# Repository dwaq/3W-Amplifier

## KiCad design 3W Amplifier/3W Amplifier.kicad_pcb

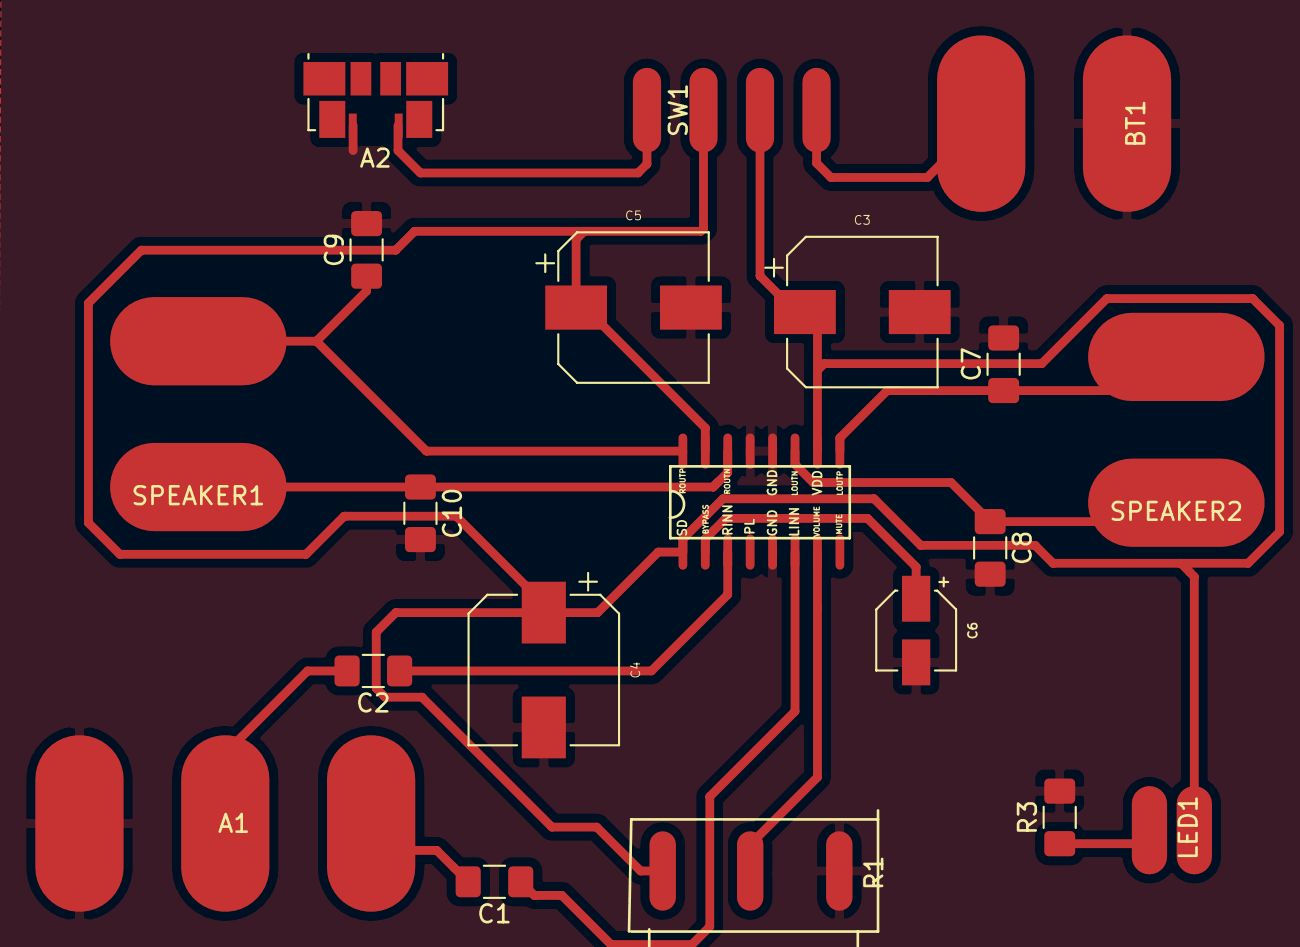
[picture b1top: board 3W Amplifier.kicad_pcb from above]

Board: 2 copper layers, 20 parts (0 on the bottom side), 15 nets.

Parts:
A1: AudioJack3_Ground; AUX CABLE
A2: USB_B_Micro; USB_Micro-B_Molex
BT1: Battery; Speaker
C1, C2: 100nf; Capacitor_1206
C3, C5: 1000uf; Capacitor-Elec-LG
C4: 220uf; Capacitor-Elec-LG
C6: 1uf; Capacitor_Electrolytic_SM
C7, C8, C9, C10: 10nf; Capacitor_1206
LED1: GREEN; LED-Through-hole
R1: 100kΩ; Potentiometer-100kohms
R3: 220Ω; Resistor
SPEAKER1, SPEAKER2: 3WATTS; Speaker
SW1: SW_DIP_x02; Switch-ES02MSABE
U1: PAM8008

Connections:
/BYPASS: C6.1, U1.2
/GND: A1.S, A2.5, BT1.2, C3.2, C4.2, C5.2, C6.2, C7.2, C8.2, C9.2, C10.2, R1.3, R3.2, U1.5, U1.12, U1.13
/LINN: C1.1, U1.6
/LOUTN: C8.1, SPEAKER2.2, U1.11
/LOUTP: C7.1, SPEAKER2.1, U1.9
/RINN: C2.1, U1.3
/ROUTN: C10.1, SPEAKER1.2, U1.14
/ROUTP: C9.1, SPEAKER1.1, U1.16
/VDD: C3.1, C4.1, C5.1, LED1.2, R1.1, SW1.2, SW1.3, U1.1, U1.10, U1.15
/VOLUME: R1.2, U1.7
unnamed: A1.R, C2.2
unnamed: A1.T, C1.2
unnamed: A2.1, SW1.1
unnamed: BT1.1, SW1.4
unnamed: LED1.1, R3.1

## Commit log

2019-04-11 Brandon's files
2019-04-11 Remove 0 ohm resistors from schematic
2019-04-12 remove backup file
2019-04-12 Correctly connect the audio jack
2019-04-12 Update from fixed location to relative location
2019-04-12 Fix LED pad spacing
2019-04-12 fix switch footprint
2019-04-12 add battery and switch to sch
2019-04-12 Apply footprints to new parts and generate netlist
2019-04-12 ignore some autogenerated files
2019-04-12 bring in new parts and delete all tracks
2019-04-12 add pad numbers to parts
2019-04-12 update footprints on PCB to use pad numbers
2019-04-12 everything routed but power
2019-04-12 add full GND pour
2019-04-12 Update USB footprint so mounting pads are seperate
2019-04-12 have most of power routed
2019-04-12 Add the shield pins back onto the USB connector and connect to GND
2019-04-12 Fully routed
2019-04-12 Moved the led, moved the USB, added margin on the left and right
2019-04-12 rotate LED and move battery connector towards center
2019-04-12 remove mounting pads from switch
    they can just be soldered to the bare copper board
